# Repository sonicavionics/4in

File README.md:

Repo for the files for the 4 inch avionics

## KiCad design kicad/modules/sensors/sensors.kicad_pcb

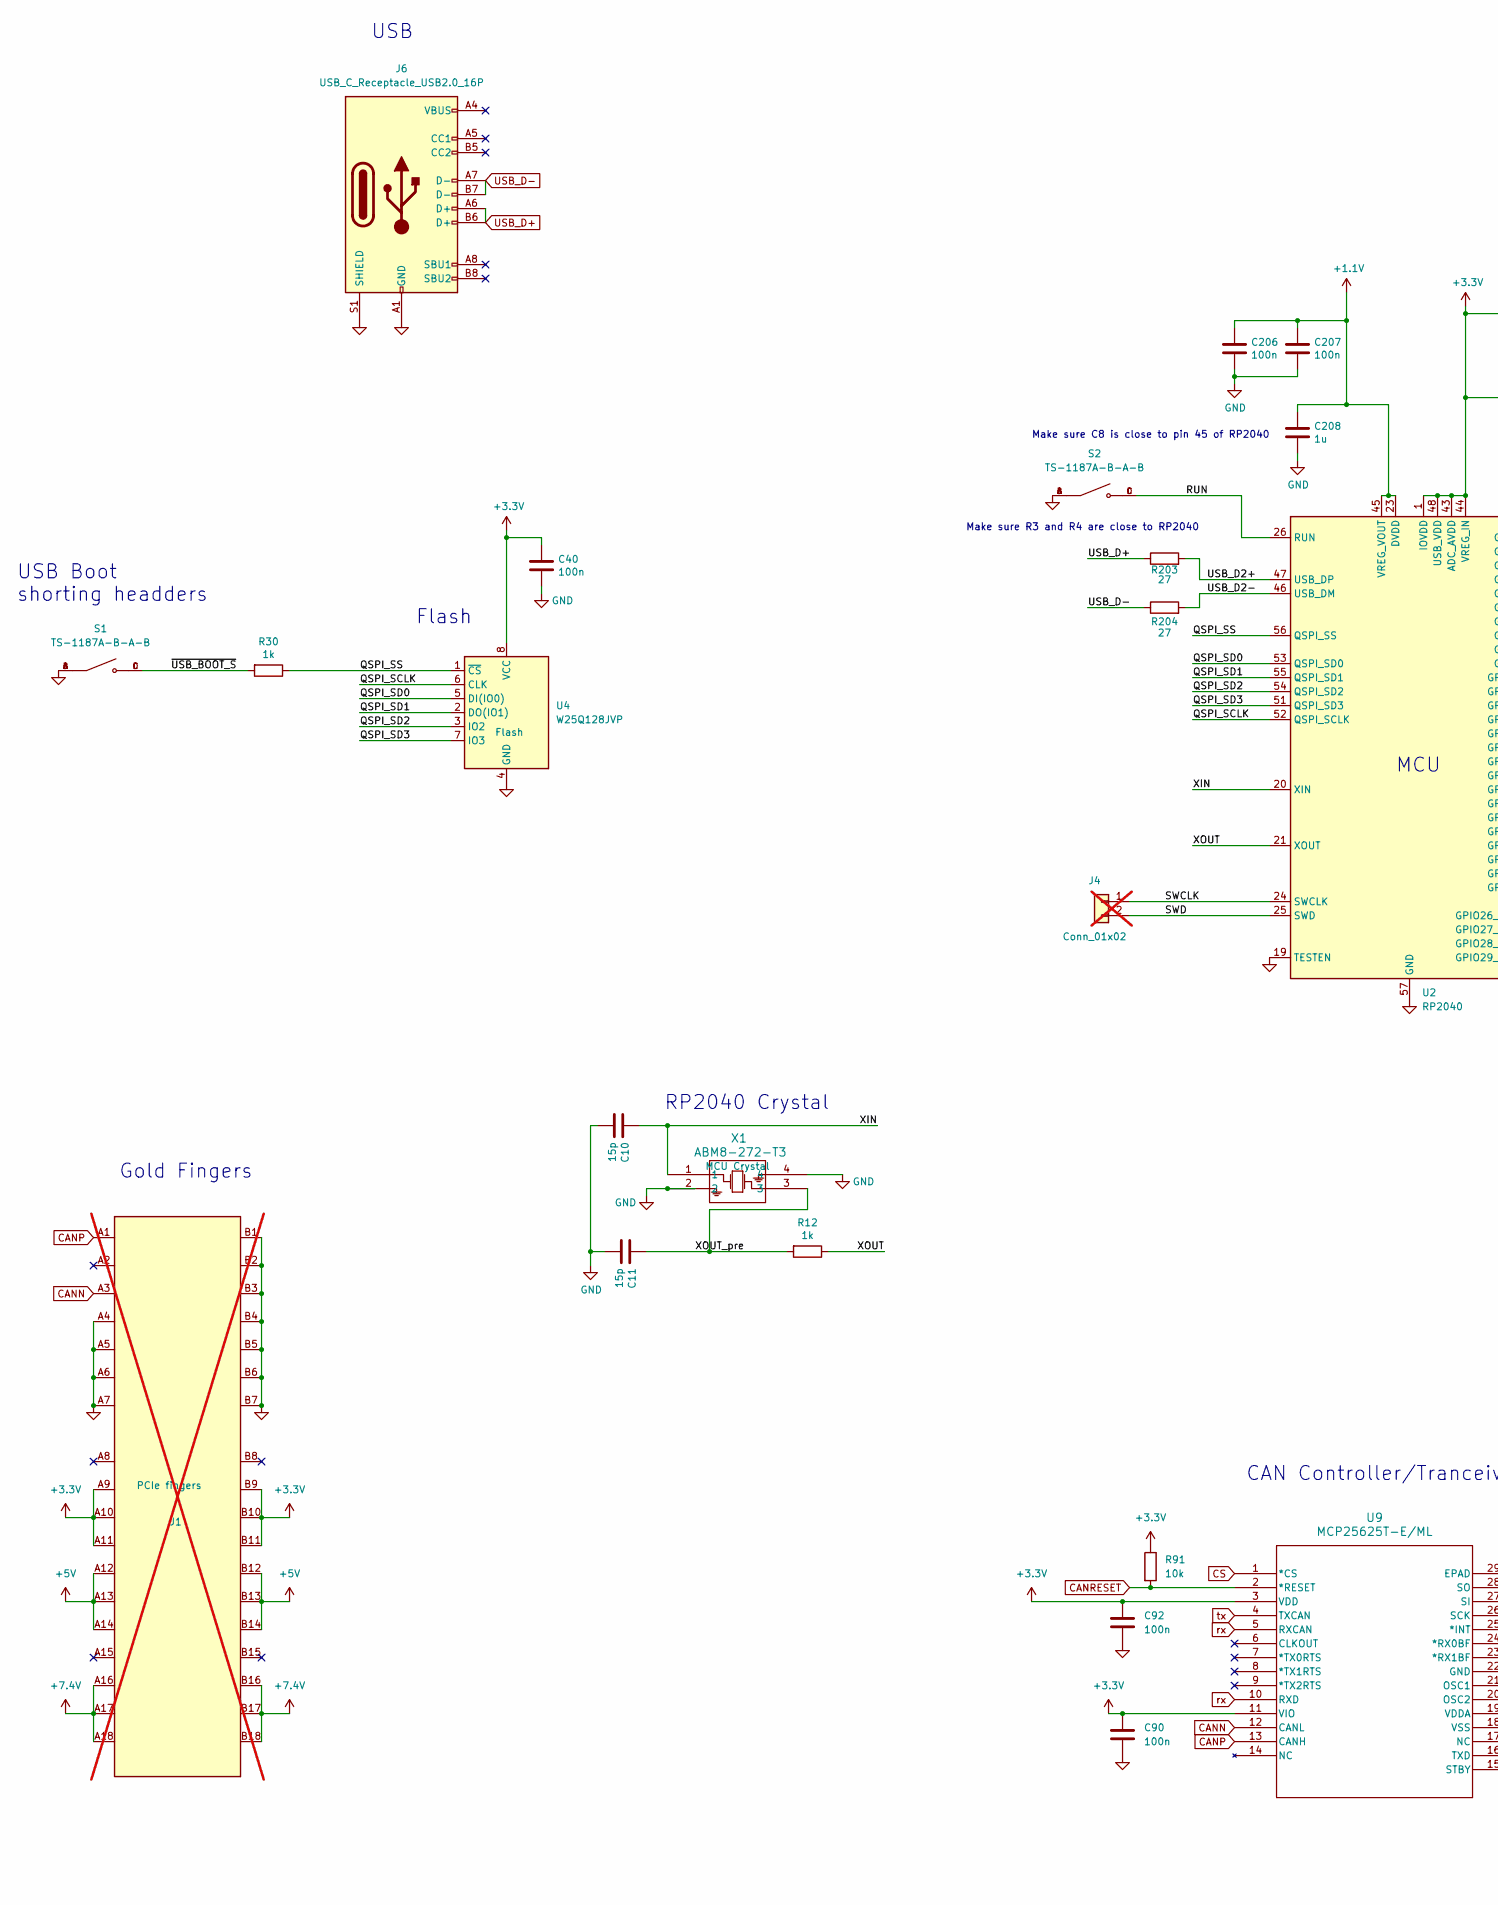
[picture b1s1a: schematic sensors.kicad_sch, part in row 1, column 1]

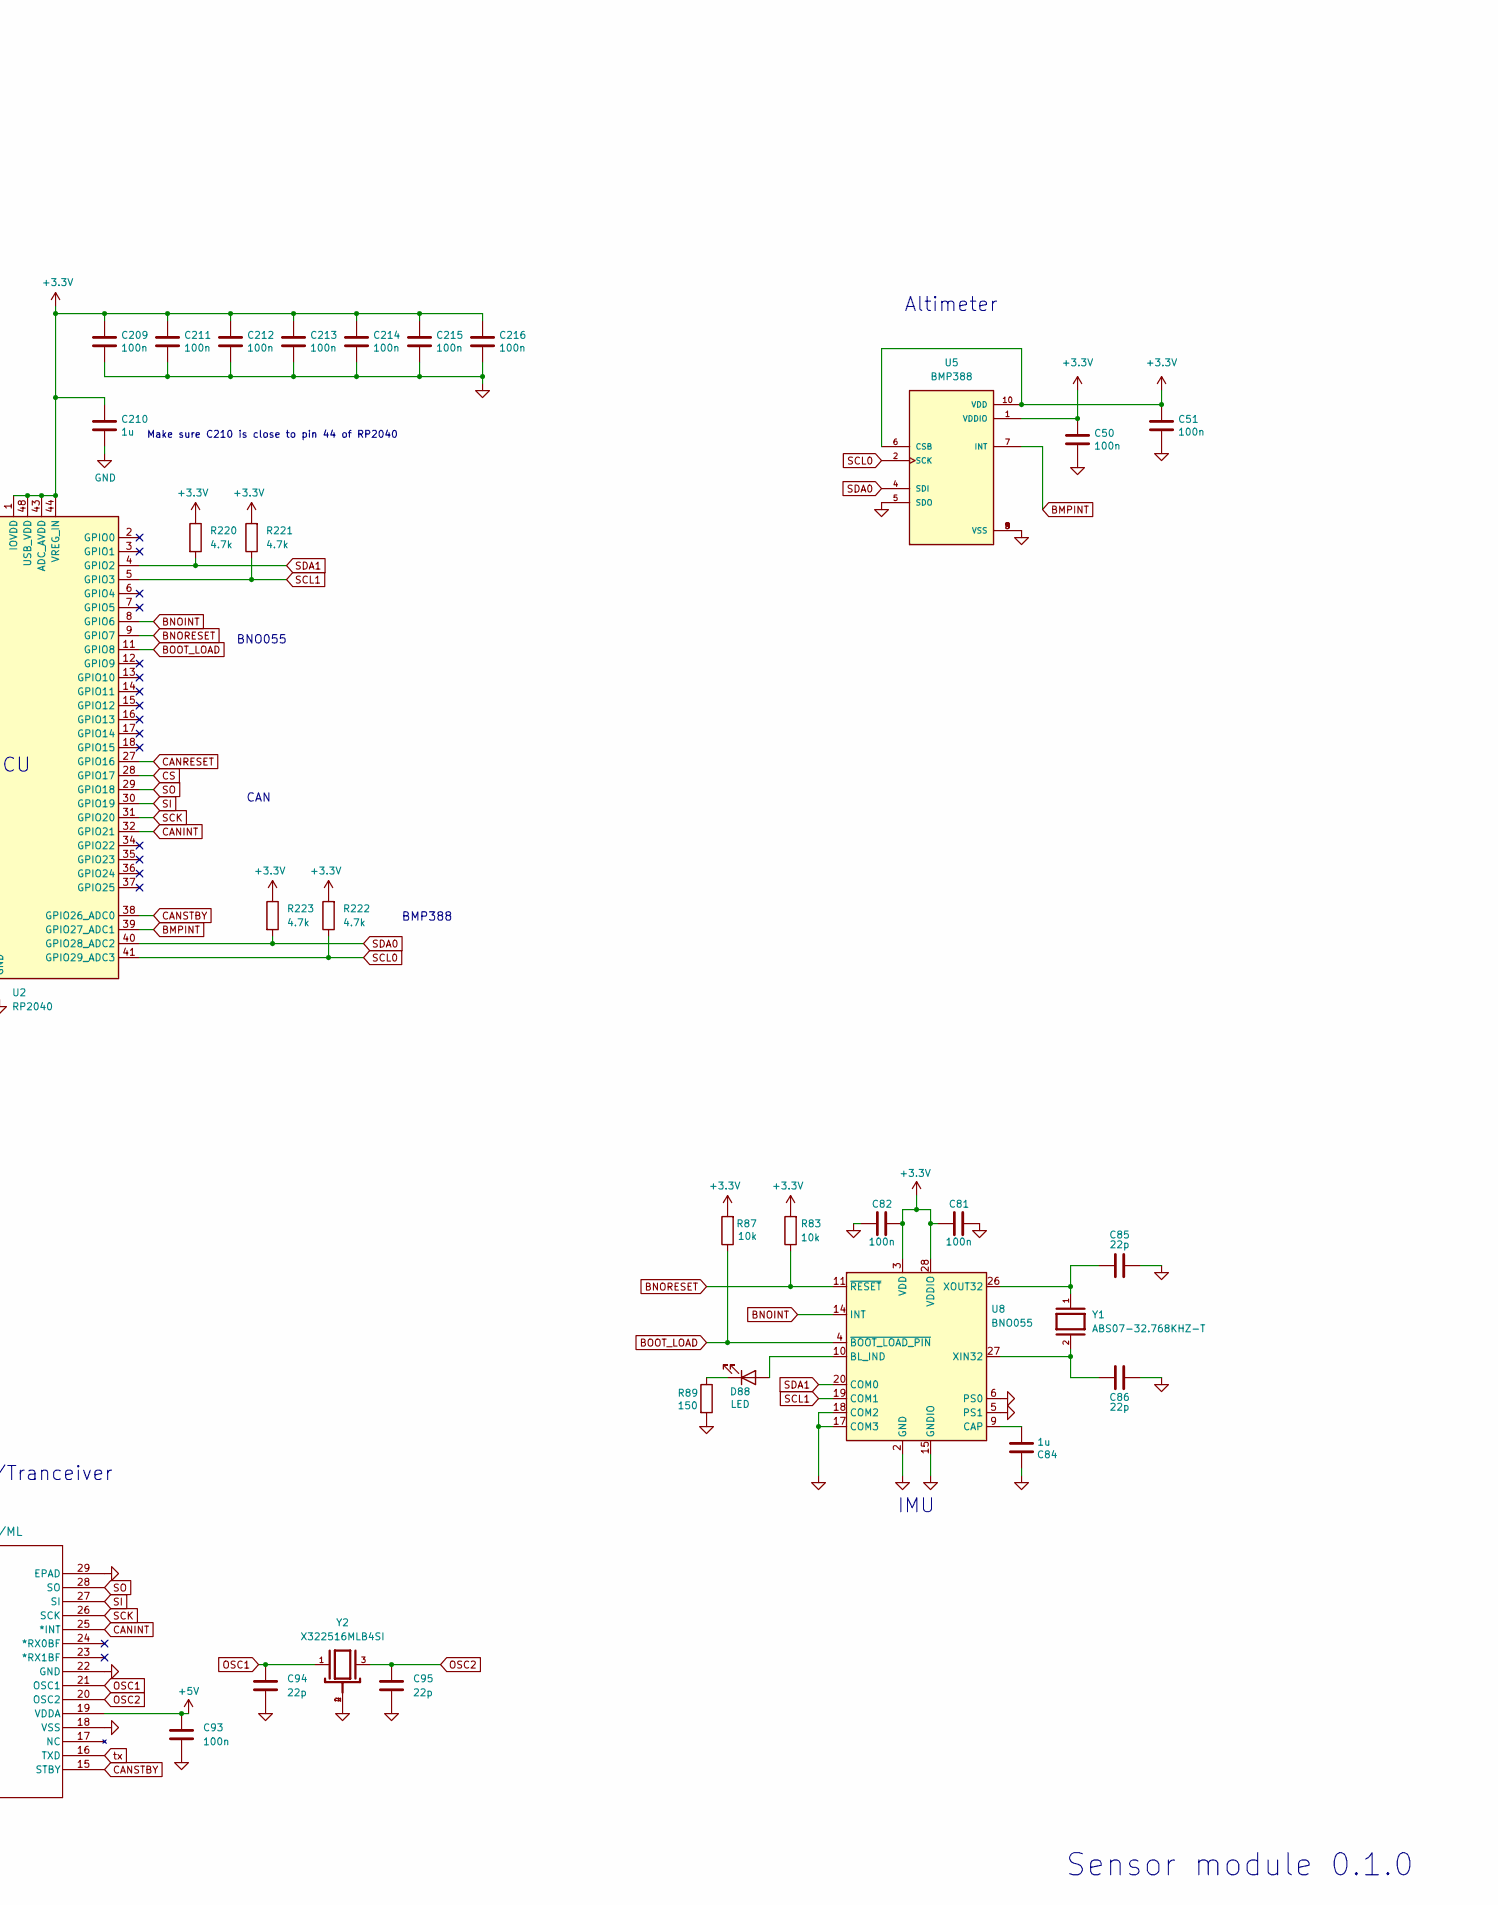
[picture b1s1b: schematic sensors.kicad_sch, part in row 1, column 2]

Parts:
C10, C11: 15p; C_0402_1005Metric; LCSC Part # C1548
C40, C50, C51, C81, C82, C90, C92, C93, C206, C207, C209, C211, C212, C213, C214, C215, C216: 100n; C_0402_1005Metric; LCSC Part # C307331
C84, C208, C210: 1u; C_0402_1005Metric; LCSC Part # C52923
C85, C86, C94, C95: 22p; C_0402_1005Metric; LCSC Part # C1555
D88: LED; LED_0603_1608Metric; LCSC Part # C2286
J1: Bus_PCI_Express_x1; BUS_PCIexpress_x1; LCSC Part # n/a; not fitted
J4: Conn_01x02; PinHeader_1x02_P2.54mm_Vertical; LCSC Part # n/a; not fitted
J6: USB_C_Receptacle_USB2.0_16P; USB_C_Receptacle_Palconn_UTC16-G; LCSC Part # C2765186
R12, R30: 1k; R_0402_1005Metric; LCSC Part # C11702
R83, R87, R91: 10k; R_0402_1005Metric; LCSC Part # C25744
R89: 150; R_0603_1608Metric; LCSC Part # C22808
R203, R204: 27; R_0402_1005Metric; LCSC Part # C25100
R220, R221, R222, R223: 4.7k; R_0402_1005Metric; LCSC Part # C25900
S1, S2: TS-1187A-B-A-B; SW_TS-1187A-B-A-B; PARTREV A0; LCSC Part # C318884
U2: RP2040; QFN-56-1EP_7x7mm_P0.4mm_EP3.2x3.2mm; LCSC C2040
U4: W25Q128JVP; WSON-8-1EP_6x5mm_P1.27mm_EP3.4x4.3mm; LCSC C190862
U5: BMP388; PQFN50P200X200X80-10N; PARTREV 1.1; LCSC Part # C779278
U8: BNO055; LGA-28_5.2x3.8mm_P0.5mm; LCSC C93216
U9: MCP25625T-E/ML; QFN28_6X6MC_MCH; LCSC Part # C191253
X1: ABM8-272-T3; ABM8-272-T3_ABR; LCSC Part # C20625731
Y1: ABS07-32.768KHZ-T; XTAL_ABS07-32.768KHZ-T; PARTREV 08.19.15; LCSC Part # C130253
Y2: X322516MLB4SI; OSC_X322516MLB4SI; PARTREV N/A; LCSC Part # C12668

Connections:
+1.1V: C206.1, C207.1, C208.1, U2.23 (DVDD), U2.45 (VREG_VOUT), U2.50 (DVDD)
+3.3V: C40.1, C50.1, C51.1, C81.1, C82.2, C90.1, C92.1, C209.1, C210.1, C211.1, C212.1, C213.1, C214.1, C215.1, C216.1, J1.A9 (+3.3V), J1.A10 (+3.3V), J1.A11 (~PERST), J1.B9 (JTAG1), J1.B10 (3.3Vaux), J1.B11 (~WAKE), R83.2, R87.2, R91.1, R220.1, R221.2, R222.2, R223.1, U2.1 (IOVDD), U2.10 (IOVDD), U2.22 (IOVDD), U2.33 (IOVDD), U2.42 (IOVDD), U2.43 (ADC_AVDD), U2.44 (VREG_IN), U2.48 (USB_VDD), U2.49 (IOVDD), U4.8 (VCC), U5.1 (VDDIO), U5.6 (CSB), U5.10 (VDD), U8.3 (VDD), U8.28 (VDDIO), U9.3 (VDD), U9.11 (VIO)
+5V: C93.1, J1.A12 (GND), J1.A13 (REFCLK+), J1.A14 (REFCLK-), J1.B12 (RSVD), J1.B13 (GND), J1.B14 (PETp0), U9.19 (VDDA)
+7.4V: J1.A16 (PERp0), J1.A17 (PERn0), J1.A18 (GND), J1.B16 (GND), J1.B17 (~PRSNT2), J1.B18 (GND)
/QSPI_SCLK: U2.52 (QSPI_SCLK), U4.6 (CLK)
/QSPI_SD0: U2.53 (QSPI_SD0), U4.5 (DI(IO0))
/QSPI_SD1: U2.55 (QSPI_SD1), U4.2 (DO(IO1))
/QSPI_SD2: U2.54 (QSPI_SD2), U4.3 (IO2)
/QSPI_SD3: U2.51 (QSPI_SD3), U4.7 (IO3)
/QSPI_SS: R30.1, U2.56 (QSPI_SS), U4.1 (~CS)
/RUN: S2.C, S2.D, U2.26 (RUN)
/SWCLK: J4.1, U2.24 (SWCLK)
/SWD: J4.2, U2.25 (SWD)
/USB_D2+: R203.2, U2.47 (USB_DP)
/USB_D2-: R204.2, U2.46 (USB_DM)
/XIN: C10.1, U2.20 (XIN), X1.1
/XOUT: R12.1, U2.21 (XOUT)
/XOUT_pre: C11.1, R12.2, X1.3
/~USB_BOOT_S: R30.2, S1.C, S1.D
BMPINT: U2.39 (GPIO27_ADC1), U5.7 (INT)
BNOINT: U2.8 (GPIO6), U8.14 (INT)
BNORESET: R83.1, U2.9 (GPIO7), U8.11 (~RESET)
BOOT_LOAD: R87.1, U2.11 (GPIO8), U8.4 (~BOOT_LOAD_PIN)
CANINT: U2.32 (GPIO21), U9.25 (*INT)
CANN: J1.A3 (+12V), U9.12 (CANL)
CANP: J1.A1 (~PRSNT1), U9.13 (CANH)
CANRESET: R91.2, U2.27 (GPIO16), U9.2 (*RESET)
CANSTBY: U2.38 (GPIO26_ADC0), U9.15 (STBY)
CS: U2.28 (GPIO17), U9.1 (*CS)
GND: C10.2, C11.2, C40.2, C50.2, C51.2, C81.2, C82.1, C84.1, C85.2, C86.1, C90.2, C92.2, C93.2, C94.2, C95.2, C206.2, C207.2, C208.2, C209.2, C210.2, C211.2, C212.2, C213.2, C214.2, C215.2, C216.2, J1.A4 (GND), J1.A5 (JTAG2), J1.A6 (JTAG3), J1.A7 (JTAG4), J1.B1 (+12V), J1.B2 (+12V), J1.B3 (+12V), J1.B4 (GND), J1.B5 (SMCLK), J1.B6 (SMDAT), J1.B7 (GND), J6.A1 (GND), J6.A12 (GND), J6.B1 (GND), J6.B12 (GND), J6.S1 (SHIELD), R89.2, S1.A, S1.B, S2.A, S2.B, U2.19 (TESTEN), U2.57 (GND), U4.4 (GND), U5.3 (VSS), U5.5 (SDO), U5.8 (VSS), U5.9 (VSS), U8.2 (GND), U8.5 (PS1), U8.6 (PS0), U8.15 (GNDIO), U8.16 (GNDIO), U8.17 (COM3), U8.18 (COM2), U8.25 (GNDIO), U9.18 (VSS), U9.22 (GND), U9.29 (EPAD), X1.2, X1.4, Y2.2, Y2.4
unnamed: D88.2 (A), U8.10 (BL_IND)
unnamed: D88.1 (K), R89.1
unnamed: C84.2, U8.9 (CAP)
unnamed: C86.2, U8.27 (XIN32), Y1.2
unnamed: C85.1, U8.26 (XOUT32), Y1.1
OSC1: C94.1, U9.21 (OSC1), Y2.1
OSC2: C95.1, U9.20 (OSC2), Y2.3
SCK: U2.31 (GPIO20), U9.26 (SCK)
SCL0: R222.1, U2.41 (GPIO29_ADC3), U5.2 (SCK)
SCL1: R221.1, U2.5 (GPIO3), U8.19 (COM1)
SDA0: R223.2, U2.40 (GPIO28_ADC2), U5.4 (SDI)
SDA1: R220.2, U2.4 (GPIO2), U8.20 (COM0)
SI: U2.30 (GPIO19), U9.27 (SI)
SO: U2.29 (GPIO18), U9.28 (SO)
USB_D+: J6.A6 (D+), J6.B6 (D+), R203.1
USB_D-: J6.A7 (D-), J6.B7 (D-), R204.1
rx: U9.5 (RXCAN), U9.10 (RXD)
tx: U9.4 (TXCAN), U9.16 (TXD)

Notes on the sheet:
Make sure C210 is close to pin 44 of RP2040
Make sure C8 is close to pin 45 of RP2040
RP2040 Crystal
Altimeter
BNO055
BMP388
IMU
USB
Make sure R3 and R4 are close to RP2040
CAN
USB Boot shorting headders
Sensor module 0.1.0
Gold Fingers
MCU
CAN Controller/Tranceiver
Flash

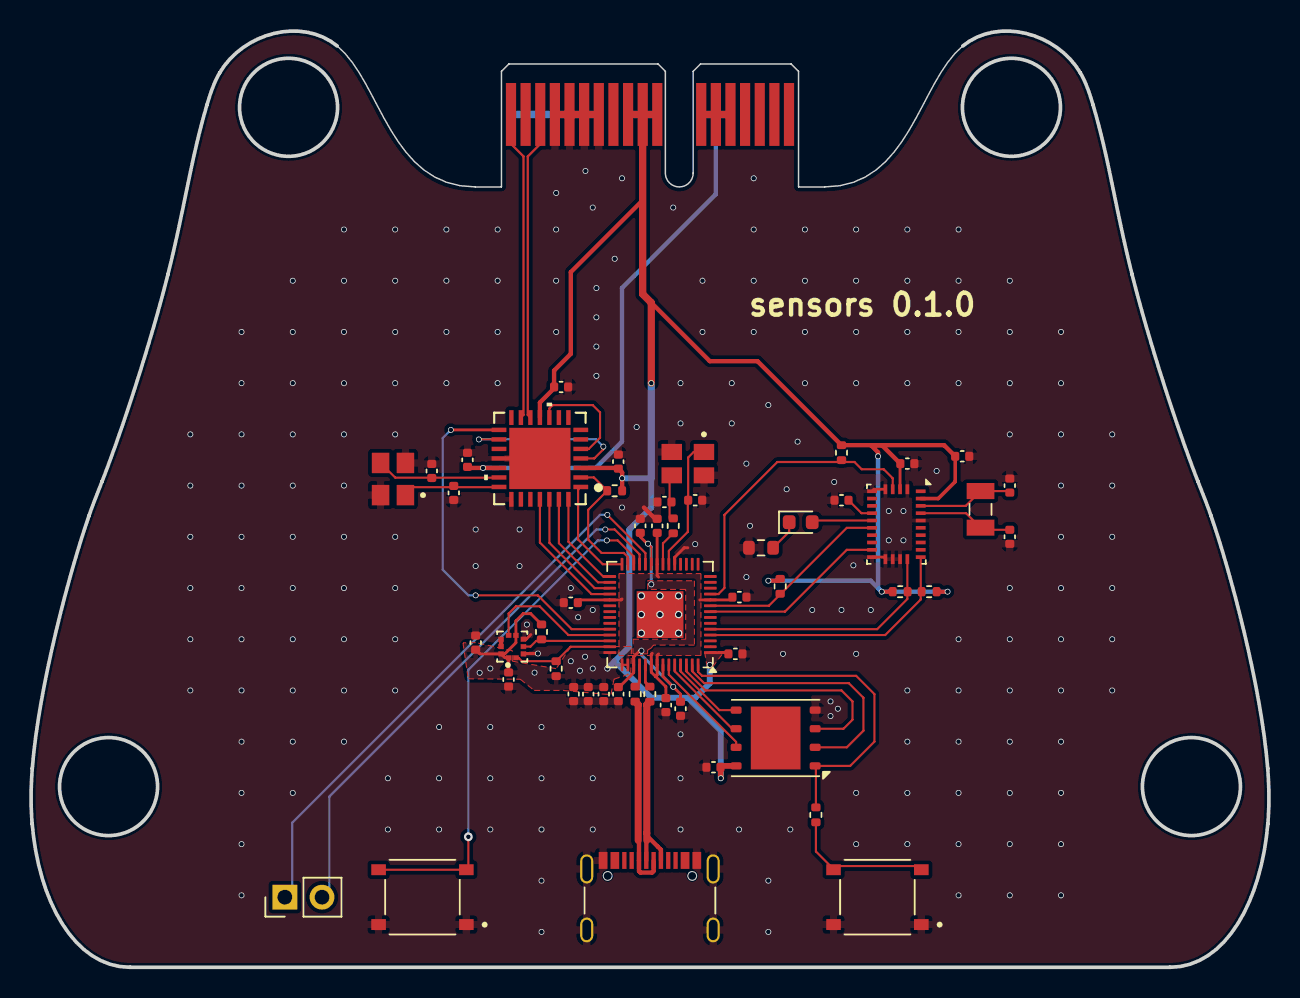
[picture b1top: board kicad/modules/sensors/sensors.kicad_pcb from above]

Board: 2 copper layers, 84.6 x 64.0 mm, 52 parts (1 on the bottom side), 48 nets.

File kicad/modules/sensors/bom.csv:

"Reference","info","Value","notes","Footprint","LCSC Part #","JLC Link","Digikey Link","basic?","price","Current Draw","Qty","DNP"
"Y2","CAN Clock","X322516MLB4SI","","X322516MLB4SI:OSC_X322516MLB4SI","C12668","https://jlcpcb.com/partdetail/Yxc_CrystalOscillators-X322516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","","no","C$0.0829","200 uW 3.3v","1",""
"Y1","BNO055 Crystal","ABS07-32.768KHZ-T","","ABS07-32.768KHZ-T:XTAL_ABS07-32.768KHZ-T","C130253","https://jlcpcb.com/partdetail/AbraconLlc-ABS07_32_768KHZT/C130253","","no","C$0.6839 ","0.5 uW 3.3v","1",""
"X1","MCU Crystal","ABM8-272-T3","","ABM8-272-T3:ABM8-272-T3_ABR","C20625731","https://jlcpcb.com/partdetail/AbraconLlc-ABM8_272T3/C20625731","","no","C$0.6692 ","200 uW 3.3v","1",""
"U9","CAN Controller/Tranceiver","MCP25625T-E/ML","","MCP25625T_E_ML:QFN28_6X6MC_MCH","C191253","https://jlcpcb.com/partdetail/MicrochipTech-MCP25625T_EML/C191253","","no","C$2.9424 ","Con=10mA, Tra=70mA","1",""
"U8","BNO055","BNO055","","Package_LGA:LGA-28_5.2x3.8mm_P0.5mm","C93216","https://jlcpcb.com/partdetail/BoschSensortec-BNO055/C93216","","no","C$14.0435 ","12.3mA","1",""
"U5","BMP388","BMP388","","BMP388:PQFN50P200X200X80-10N","C779278","https://jlcpcb.com/partdetail/BoschSensortec-BMP388/C779278","","no"," C$2.3423 ","800uA","1",""
"U4","Flash","W25Q128JVP","","Package_SON:WSON-8-1EP_6x5mm_P1.27mm_EP3.4x4.3mm","C190862","https://jlcpcb.com/partdetail/WinbondElec-W25Q128JVPIQ/C190862","","no","C$1.0737 ","25mA","1",""
"U2","MCU","RP2040","","Package_DFN_QFN:QFN-56-1EP_7x7mm_P0.4mm_EP3.2x3.2mm","C2040","https://jlcpcb.com/partdetail/RaspberryPi-RP2040/C2040","","no","C$1.4190 ","20mA","1",""
"S1,S2","Button","TS-1187A-B-A-B","","TS-1187A-B-A-B:SW_TS-1187A-B-A-B","C318884","https://jlcpcb.com/partdetail/XKBConnection-TS_1187A_B_AB/C318884","","yes"," C$0.0242 ","","2",""
"R83,R87,R91","10k ohm","10k","","Resistor_SMD:R_0402_1005Metric","C25744","https://jlcpcb.com/partdetail/26487-0402WGF1002TCE/C25744","","yes","C$0.0007 ","","3",""
"R220,R221,R222,R223","4.7k ohm","4.7k","","Resistor_SMD:R_0402_1005Metric","C25900","https://jlcpcb.com/partdetail/26643-0402WGF4701TCE/C25900","","yes","C$0.0007 ","","4",""
"R203,R204","27 ohm","27","","Resistor_SMD:R_0603_1608Metric","C25190","https://jlcpcb.com/partdetail/25933-0603WAF270JT5E/C25190","","extended prefered","C$0.0013","","2",""
"R12,R30","1k ohm","1k","","Resistor_SMD:R_0402_1005Metric","C11702","https://jlcpcb.com/partdetail/12256-0402WGF1001TCE/C11702","","yes","C$0.0007","","2",""
"R89","150 ohm","150","","Resistor_SMD:R_0603_1608Metric","C22808","https://jlcpcb.com/partdetail/23535-0603WAF1500T5E/C22808","","yes","C$0.0013 ","","1",""
"J4","two headders","Conn_01x02","","Connector_PinHeader_2.54mm:PinHeader_1x02_P2.54mm_Vertical","n/a","n/a","","n/a","n/a","","1","DNP"
"J2","USB-C","TYPE-C-31-M-04","","TYPE-C-31-M-04:HRO_TYPE-C-31-M-04","C129018","https://jlcpcb.com/partdetail/Korean_HropartsElec-TYPE_C_31_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","","no","C$0.8196 ","","1",""
"J1","PCIe fingers","Bus_PCI_Express_x1","","Connector_PCBEdge:BUS_PCIexpress_x1","n/a","n/a","","n/a","n/a","","1","DNP"
"D88","Red LED","LED","","LED_SMD:LED_0603_1608Metric","C2286","https://jlcpcb.com/partdetail/Hubei_KentoElec-KT0603R/C2286","","yes","C$0.0075 ","","1",""
"C85,C86","22pF Cap","22p","","Capacitor_SMD:C_0402_1005Metric","C1555","https://jlcpcb.com/partdetail/1907-0402CG220J500NT/C1555","","yes","C$0.0013 ","","2",""
"C84,C208,C210","1uF Cap","1u","","Capacitor_SMD:C_0402_1005Metric","C52923","https://jlcpcb.com/partdetail/53938-CL05A105KA5NQNC/C52923","","yes","C$0.0041 ","","3",""
"C40,C50,C51,C81,C82,C90,C206,C207,C209,C211,C212,C213,C214,C215,C216","100nF Cap","100n","","Capacitor_SMD:C_0402_1005Metric","C307331","https://jlcpcb.com/partdetail/291005-CL05B104KB54PNC/C307331","","yes","C$0.0077 ","","15",""
"C10,C11","15pF Cap","15p","","Capacitor_SMD:C_0402_1005Metric","C1548","https://jlcpcb.com/partdetail/1900-0402CG150J500NT/C1548","","yes","C$0.0013 ","","2",""

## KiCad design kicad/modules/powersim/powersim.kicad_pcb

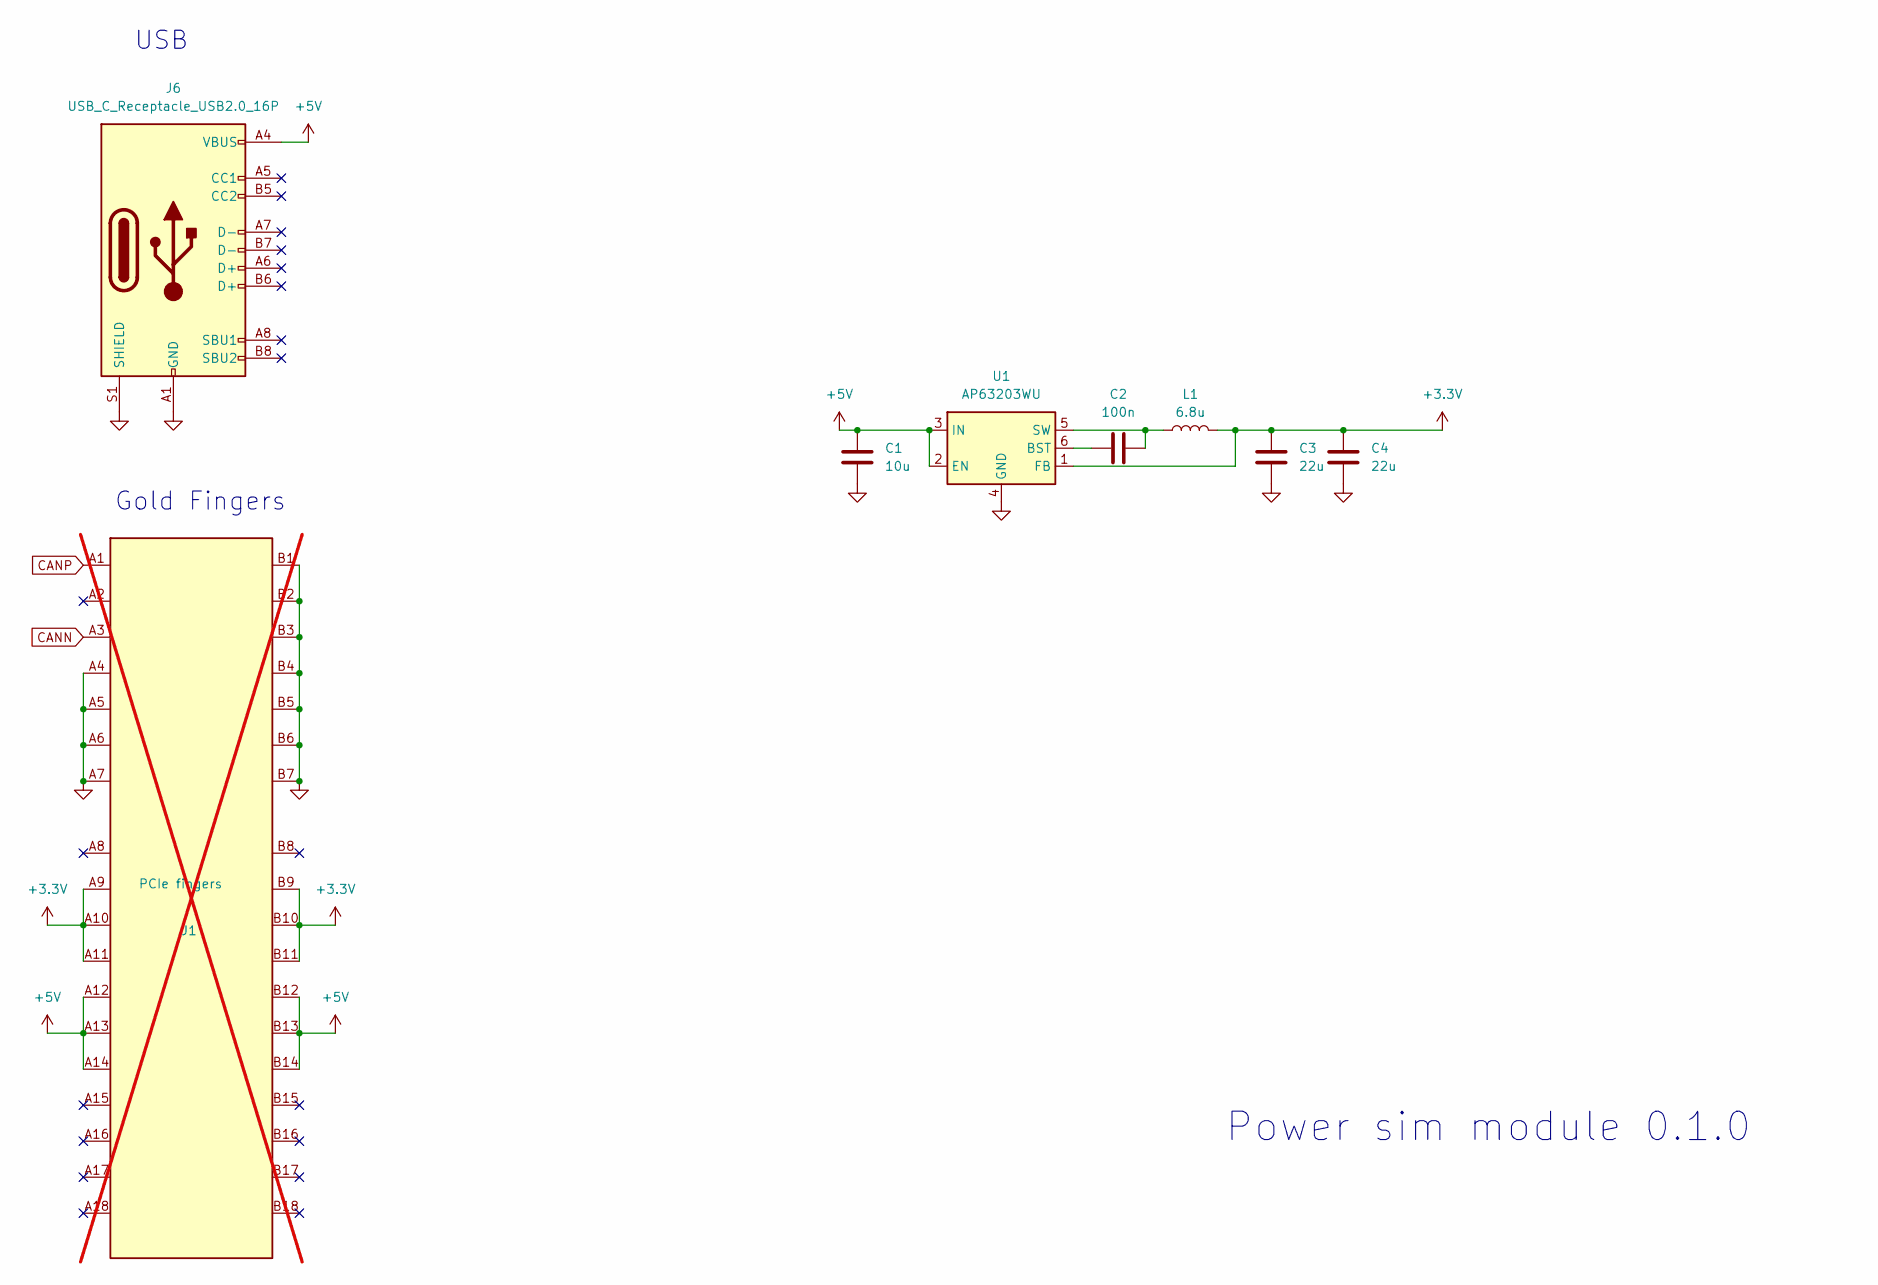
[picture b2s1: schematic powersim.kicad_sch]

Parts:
C1: 10u
C2: 100n
C3, C4: 22u
J1: Bus_PCI_Express_x1; BUS_PCIexpress_x1; LCSC Part # n/a; not fitted
J6: USB_C_Receptacle_USB2.0_16P; USB_C_Receptacle_Palconn_UTC16-G; LCSC Part # C2765186
L1: 6.8u
U1: AP63203WU; TSOT-23-6; LCSC Part # C780769

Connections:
+3.3V: C3.1, C4.1, J1.A9 (+3.3V), J1.A10 (+3.3V), J1.A11 (~PERST), J1.B9 (JTAG1), J1.B10 (3.3Vaux), J1.B11 (~WAKE), L1.2, U1.1 (FB)
+5V: C1.1, J1.A12 (GND), J1.A13 (REFCLK+), J1.A14 (REFCLK-), J1.B12 (RSVD), J1.B13 (GND), J1.B14 (PETp0), J6.A4 (VBUS), J6.A9 (VBUS), J6.B4 (VBUS), J6.B9 (VBUS), U1.2 (EN), U1.3 (IN)
CANN: J1.A3 (+12V); also elsewhere on the board
CANP: J1.A1 (~PRSNT1); also elsewhere on the board
GND: C1.2, C3.2, C4.2, J1.A4 (GND), J1.A5 (JTAG2), J1.A6 (JTAG3), J1.A7 (JTAG4), J1.B1 (+12V), J1.B2 (+12V), J1.B3 (+12V), J1.B4 (GND), J1.B5 (SMCLK), J1.B6 (SMDAT), J1.B7 (GND), J6.A1 (GND), J6.A12 (GND), J6.B1 (GND), J6.B12 (GND), J6.S1 (SHIELD), U1.4 (GND)
unnamed: C2.1, U1.6 (BST)
unnamed: C2.2, L1.1, U1.5 (SW)

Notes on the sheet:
USB
Power sim module 0.1.0
Gold Fingers

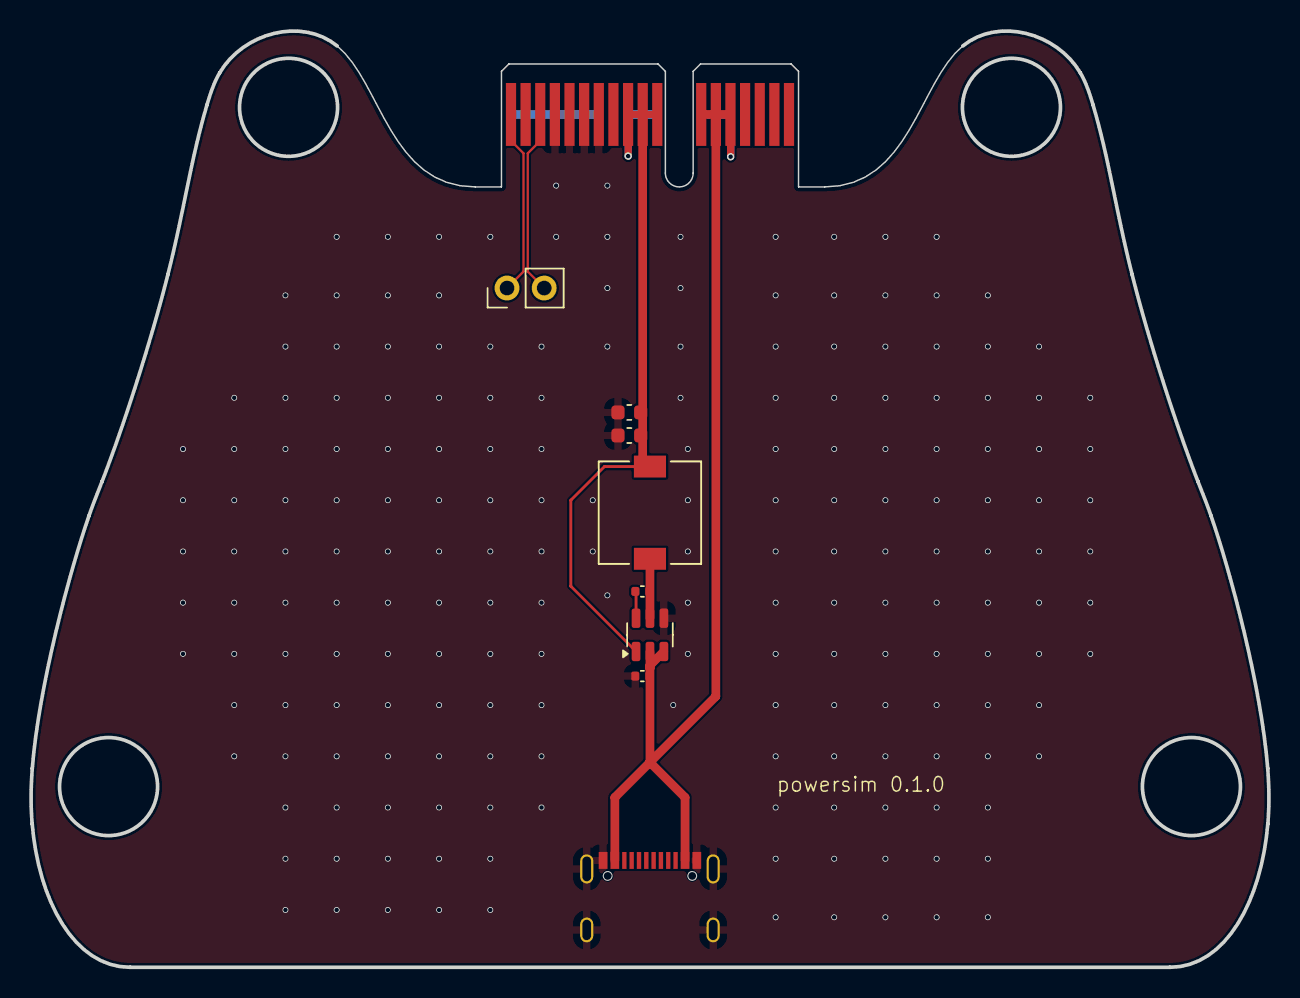
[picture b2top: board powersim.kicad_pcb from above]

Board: 2 copper layers, 84.6 x 64.0 mm, 9 parts (1 on the bottom side), 7 nets.

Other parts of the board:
J2: Conn_01x02_Pin; PinHeader_1x02_P2.54mm_Vertical

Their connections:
CANN: J2.2; also elsewhere on the board
CANP: J2.1; also elsewhere on the board

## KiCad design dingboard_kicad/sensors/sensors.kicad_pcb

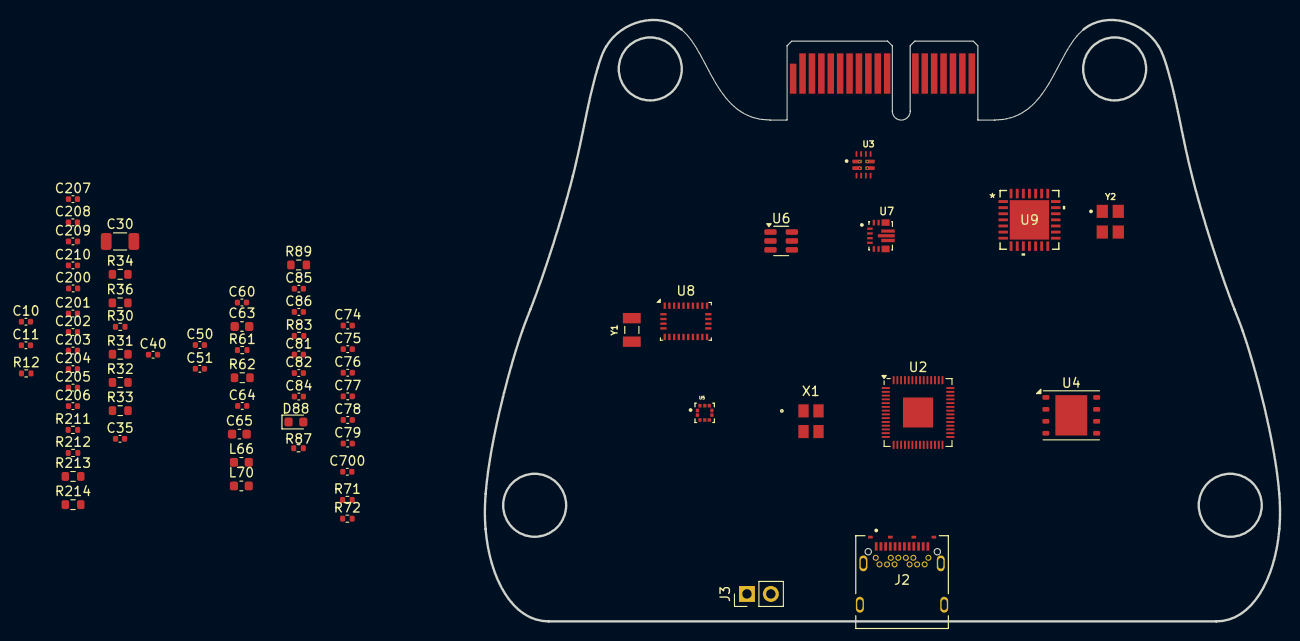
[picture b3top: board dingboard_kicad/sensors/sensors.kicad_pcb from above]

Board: 2 copper layers, 84.6 x 64.0 mm, 69 parts (1 on the bottom side), 51 nets, no tracks yet.

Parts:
C10, C11: 15p; C_0402_1005Metric
C30: 100u; C_1206_3216Metric
C35: 0.01u; C_0402_1005Metric
C40, C50, C51, C60, C81, C82, C200, C201, C202, C203, C204, C205, C206, C207, C208: 100n; C_0402_1005Metric
C63, C65: 10uF/25v; C_0603_1608Metric
C64: 2.2u; C_0402_1005Metric
C74, C75, C76: 10uF; C_0402_1005Metric
C77, C78, C79: 22u; C_0402_1005Metric
C84, C209, C210: 1u; C_0402_1005Metric
C85, C86: 22p; C_0402_1005Metric
C700: 10u; C_0402_1005Metric
D88: LED; LED_0603_1608Metric
J1: Bus_PCI_Express_x1; BUS_PCIexpress_x1
J2: TYPE-C-31-M-04; HRO_TYPE-C-31-M-04
J3: Conn_01x02; PinHeader_1x02_P2.54mm_Vertical
L66: 2.2u; L_0603_1608Metric
L70: 1.5u; L_0603_1608Metric
R12, R30: 1k; R_0402_1005Metric
R31, R33: 23.7k; R_0603_1608Metric
R32, R34: 5k; R_0603_1608Metric
R36: 51.1k; R_0603_1608Metric
R61, R72: 100k; R_0402_1005Metric
R62: 22.1k; R_0603_1608Metric
R71, R83, R87: 10k; R_0402_1005Metric
R89: 150; R_0603_1608Metric
R211, R212: 4.7k; R_0402_1005Metric
R213, R214: 27; R_0603_1608Metric
U2: RP2040; QFN-56-1EP_7x7mm_P0.4mm_EP3.2x3.2mm
U3: TPS2121RUXR; IC_TPS2121RUXR
U4: W25Q128JVP; WSON-8-1EP_6x5mm_P1.27mm_EP3.4x4.3mm
U5: BMP388; PQFN50P200X200X80-10N
U6: LMR51430 1.1k FPWM; SOT-23-6
U7: TPS63070RNMR; VREG_TPS63070RNMR
U8: BNO055; LGA-28_5.2x3.8mm_P0.5mm
U9: MCP25625T-E/ML; QFN28_6X6MC_MCH
X1: ABM8-272-T3; ABM8-272-T3_ABR
Y1: ABS07-32.768KHZ-T; XTAL_ABS07-32.768KHZ-T
Y2: X322516MLB4SI; OSC_X322516MLB4SI

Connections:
+1V1: C207.1, C208.1, C209.1, U2.23 (DVDD), U2.45 (VREG_VOUT), U2.50 (DVDD)
+3.3V: C50.1, C51.1, C63.1, C65.1, L66.2, R61.1, U5.1 (VDDIO), U5.6 (CSB), U5.10 (VDD), U9.3 (VDD), U9.11 (VIO)
+3V3: C40.1, C81.1, C82.2, C200.1, C201.1, C202.1, C203.1, C204.1, C205.1, C206.1, C210.1, R83.2, R87.2, R211.1, R212.2, U2.1 (IOVDD), U2.10 (IOVDD), U2.22 (IOVDD), U2.33 (IOVDD), U2.42 (IOVDD), U2.43 (ADC_AVDD), U2.44 (VREG_IN), U2.48 (USB_VDD), U2.49 (IOVDD), U4.8 (VCC), U8.3 (VDD), U8.28 (VDDIO)
+5V: C77.1, C78.1, C79.1, C700.1, R72.2, U7.5 (FB), U7.7_8 (VOUT), U9.19 (VDDA)
/QSPI_SCLK: U2.52 (QSPI_SCLK), U4.6 (CLK)
/QSPI_SS: R30.1, U2.56 (QSPI_SS), U4.1 (~CS)
/XIN: C10.1, U2.20 (XIN), X1.1
/XOUT: R12.1, U2.21 (XOUT)
/~USB_BOOT_S: J3.1, R30.2
BMPINT: U2.5 (GPIO3), U5.7 (INT)
BNOINT: U2.8 (GPIO6), U8.14 (INT)
BNORESET: R83.1, U2.9 (GPIO7), U8.11 (~RESET)
BOOT_LOAD: R87.1, U2.11 (GPIO8), U8.4 (~BOOT_LOAD_PIN)
CANH: J1.A9 (+3.3V), J1.B9 (JTAG1), U9.13 (CANH)
CANINT: U2.28 (GPIO17), U9.25 (*INT)
CANL: J1.A8 (JTAG5), J1.B8 (+3.3V), U9.12 (CANL)
CANSTBY: U2.27 (GPIO16), U9.15 (STBY)
CS: U2.16 (GPIO13), U9.1 (*CS)
GND: C10.2, C11.2, C30.2, C35.2, C40.2, C50.2, C51.2, C63.2, C64.2, C65.2, C74.2, C75.2, C76.2, C77.2, C78.2, C79.2, C81.2, C82.1, C84.1, C85.2, C86.1, C200.2, C201.2, C202.2, C203.2, C204.2, C205.2, C206.2, C207.2, C208.2, C209.2, C210.2, C700.2, J1.A16 (PERp0), J1.A17 (PERn0), J1.A18 (GND), J1.B16 (GND), J1.B17 (~PRSNT2), J1.B18 (GND), J2.A1 (GND_A), J2.A12 (GND_A), J2.B1 (GND_B), J2.B12 (GND_B), J2.S1 (SHIELD), J2.S2 (SHIELD), J2.S3 (SHIELD), J2.S4 (SHIELD), J2.S5 (SHIELD), J2.S6 (SHIELD), J2.S7 (SHIELD), J2.S8 (SHIELD), J3.2, R32.2, R34.2, R36.2, R62.2, R89.2, U2.57 (GND), U3.3 (CP2), U3.6 (PR1), U3.9 (ST), U3.12 (GND), U4.4 (GND), U5.3 (VSS), U5.5 (SDO), U5.8 (VSS), U5.9 (VSS), U6.1 (GND), U7.4 (GND), U7.6 (FB2), U7.10 (PGND), U7.15 (VSEL), U8.2 (GND), U8.5 (PS1), U8.6 (PS0), U8.15 (GNDIO), U8.16 (GNDIO), U8.17 (COM3), U8.18 (COM2), U8.25 (GNDIO), U9.18 (VSS), U9.22 (GND), U9.29 (EPAD), X1.2, X1.4
unnamed: C11.1, R12.2, X1.3
unnamed: D88.2 (A), U8.10 (BL_IND)
unnamed: D88.1 (K), R89.1
unnamed: R214.2, U2.46 (USB_DM)
unnamed: R213.2, U2.47 (USB_DP)
unnamed: R36.1, U3.10 (ILIM)
unnamed: R31.2, R32.1, U3.5 (OV1)
unnamed: R33.2, R34.1, U3.4 (OV2)
unnamed: C35.1, U3.11 (SS)
unnamed: C60.1, U6.6 (CB)
unnamed: R61.2, R62.1, U6.4 (FB)
unnamed: C60.2, L66.1, U6.2 (SW)
unnamed: R71.2, U7.1 (PS/SYNC), U7.14 (EN)
unnamed: L70.1, U7.11 (L1)
unnamed: L70.2, U7.9 (L2)
unnamed: R72.1, U7.2 (PG)
unnamed: C84.2, U8.9 (CAP)
unnamed: C86.2, U8.27 (XIN32), Y1.2
unnamed: C85.1, U8.26 (XOUT32), Y1.1
unnamed: Y2.2, Y2.4
SCK: U2.17 (GPIO14), U9.26 (SCK)
SCL: R212.1, U2.3 (GPIO1), U5.2 (SCK), U8.19 (COM1)
SDA: R211.2, U2.2 (GPIO0), U5.4 (SDI), U8.20 (COM0)
SI: U2.14 (GPIO11), U9.27 (SI)
SO: U2.15 (GPIO12), U9.28 (SO)
UDB_D+: J2.A6 (DP1), J2.B6 (DP2)
UDB_D-: J2.A7 (DN1), J2.B7 (DN2)
VBM: J1.A1 (~PRSNT1), J1.A2 (+12V), J1.A3 (+12V), J1.B1 (+12V), J1.B2 (+12V), J1.B3 (+12V), R33.1, U3.2 (IN2), U3.2_1 (IN2__1)
VBUS: J2.A4 (VBUS_A), J2.A9 (VBUS_A), J2.B4 (VBUS_B), J2.B9 (VBUS_B), R31.1, U3.7 (IN1), U3.7_1 (IN1__1)
rx: U9.5 (RXCAN), U9.10 (RXD)
tx: U9.4 (TXCAN), U9.16 (TXD)
vpre: C30.1, C64.1, C74.1, C75.1, C76.1, R71.1, U3.1 (OUT), U3.1_1 (OUT__1), U3.8 (OUT__2), U3.8_1 (OUT__3), U6.3 (VIN), U6.5 (EN), U7.12_13 (VIN)

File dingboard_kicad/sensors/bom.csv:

"info","Value","Reference","Footprint","LCSC Part #","link","basic?","price","Qty","DNP"
"15pF Cap","15p","C10,C11","Capacitor_SMD:C_0402_1005Metric","C1548","https://jlcpcb.com/partdetail/1900-0402CG150J500NT/C1548","yes","C$0.0013 ","2",""
"0.01uF Cap","0.01u","C35","Capacitor_SMD:C_0402_1005Metric","C15195","https://jlcpcb.com/partdetail/15869-CL05B103KB5NNNC/C15195","yes","C$0.0017 ","1",""
"100nF Cap","100n","C40,C50,C51,C60,C81,C82,C200,C201,C202,C203,C204,C205,C206,C207,C208","Capacitor_SMD:C_0402_1005Metric","C307331","https://jlcpcb.com/partdetail/291005-CL05B104KB54PNC/C307331","yes","C$0.0077 ","15",""
"1uF Cap","1u","C209,C210","Capacitor_SMD:C_0402_1005Metric","C52923","https://jlcpcb.com/partdetail/53938-CL05A105KA5NQNC/C52923","yes","C$0.0041 ","2",""
"2.2uF Cap","2.2u","C64","Capacitor_SMD:C_0402_1005Metric","C12530","https://jlcpcb.com/partdetail/13164-CL05A225MQ5NSNC/C12530","yes","C$0.0031 ","1",""
"100uF Cap","100u","C30","Capacitor_SMD:C_1206_3216Metric","C15008","https://jlcpcb.com/partdetail/15681-CL31A107MQHNNNE/C15008","yes","C$0.0830 ","1",""
"27 ohm","27","R213,R214","Resistor_SMD:R_0603_1608Metric","C25190","https://jlcpcb.com/partdetail/25933-0603WAF270JT5E/C25190","extended prefered","C$0.0013","2",""
"1k ohm","1k","R12,R30","Resistor_SMD:R_0402_1005Metric","C11702","https://jlcpcb.com/partdetail/12256-0402WGF1001TCE/C11702","yes","C$0.0007","2",""
"4.7k ohm","4.7k","R211,R212","Resistor_SMD:R_0402_1005Metric","C25900","https://jlcpcb.com/partdetail/26643-0402WGF4701TCE/C25900","yes","C$0.0007 ","2",""
"1k ohm","10k","R83","Resistor_SMD:R_0402_1005Metric","C25744","https://jlcpcb.com/partdetail/26487-0402WGF1002TCE/C25744","yes","C$0.0007 ","1",""
"22.1k ohm","22.1k","R62","0603","C25961","https://jlcpcb.com/partdetail/26704-0603WAF2212T5E/C25961","no","C$0.0013","1","DNP"
"23.7k ohm","23.7k","R31,R32,R33,R34","0603","C22912","https://jlcpcb.com/partdetail/23639-0603WAF2372T5E/C22912","no","C$0.0013 ","4","DNP"
"51.1k ohm","51.1k","R36","0603","C23072","https://jlcpcb.com/partdetail/23799-0603WAF5112T5E/C23072","no","C$0.0013 ","1","DNP"
"100k ohm","100k","R61","Resistor_SMD:R_0402_1005Metric","C25741","https://jlcpcb.com/partdetail/26484-0402WGF1003TCE/C25741","yes","C$0.0007","1",""
"20uF / 25v cap","10uF / 25v","C63,C65","0603","C96446","https://jlcpcb.com/partdetail/97651-CL10A106MA8NRNC/C96446","yes","C$0.0226","2",""
"Crystal","ABM8-272-T3","X1","crystal:ABM8-272-T3_ABR","C20625731","https://jlcpcb.com/partdetail/AbraconLlc-ABM8_272T3/C20625731","no","C$0.6692 ","1",""
"Altimeter","BMP388","U5","BMP388:PQFN50P200X200X80-10N","C779278","https://jlcpcb.com/partdetail/BoschSensortec-BMP388/C779278","no"," C$2.3423 ","1",""
"IMU","BNO055","U8","Package_LGA:LGA-28_5.2x3.8mm_P0.5mm","C93216","https://jlcpcb.com/partdetail/BoschSensortec-BNO055/C93216","no","C$14.0435 ","1",""
"PCIe fingers","Bus_PCI_Express_x1","J1","Connector_PCBEdge:BUS_PCIexpress_x1","n/a","n/a","n/a","n/a","1",""
"two headders","Conn_01x02","J3","Connector_PinHeader_2.54mm:PinHeader_1x02_P2.54mm_Vertical","n/a","n/a","n/a","n/a","1",""
"DC-DC Converter","LMR51430 1.1k FPWM","U6","Package_TO_SOT_SMD:SOT-23-6","C5219261","https://jlcpcb.com/partdetail/TexasInstruments-LMR51430YFDDC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","no","C$1.4952 ","1",""
"CAN Transceiver","MCP25625-x-SS","U7","Package_SO:SSOP-28_5.3x10.2mm_P0.65mm","C184944","https://jlcpcb.com/partdetail/MicrochipTech-MCP25625_ESS/C184944","","C$6.0709 ","1",""
"MCU","RP2040","U2","Package_DFN_QFN:QFN-56-1EP_7x7mm_P0.4mm_EP3.2x3.2mm","C2040","https://jlcpcb.com/partdetail/RaspberryPi-RP2040/C2040","no","C$1.4190 ","1",""
"Power MUX","TPS2121RUXR","U3","TPS2121RUXR:IC_TPS2121RUXR","C485916","https://jlcpcb.com/partdetail/TexasInstruments-TPS2121RUXR/C485916","","C$1.3394 ","1",""
"USB-C","TYPE-C-31-M-04","J2","TYPE-C-31-M-04:HRO_TYPE-C-31-M-04","C129018","https://jlcpcb.com/partdetail/Korean_HropartsElec-TYPE_C_31_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","no","C$0.8196 ","1",""
"Flash","W25Q128JVP","U4","Package_SON:WSON-8-1EP_6x5mm_P1.27mm_EP3.4x4.3mm","C190862","https://jlcpcb.com/partdetail/WinbondElec-W25Q128JVPIQ/C190862","no","C$1.0737 ","1",""
